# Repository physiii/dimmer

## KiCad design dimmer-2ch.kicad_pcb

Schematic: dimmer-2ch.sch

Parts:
J1: Conn_01x07; PinHeader_1x07_P2.54mm_Vertical
J2: Conn_01x03; SolderWirePad_1x03_P7.62mm_Drill2.5mm
J3: Conn_01x03; PinHeader_1x03_P2.54mm_Vertical

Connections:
/5V: J1.3, J1.4; also elsewhere on the board
/LINE_IN: J2.2, J3.3; also elsewhere on the board
/LINE_OUT_1: J2.3; also elsewhere on the board
/LINE_OUT_2: J2.1; also elsewhere on the board
/NEUTRAL: J3.1, J3.2; also elsewhere on the board
GND: J1.1, J1.2; also elsewhere on the board

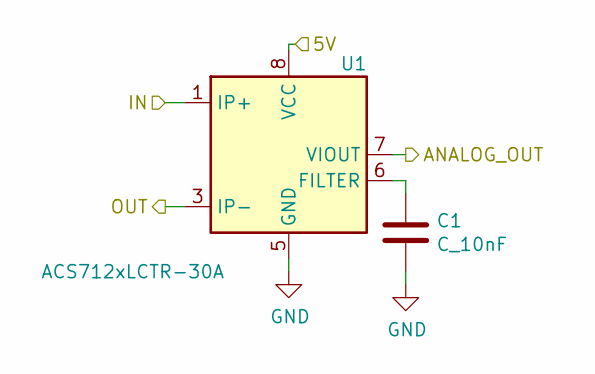
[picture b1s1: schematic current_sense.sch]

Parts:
C1: C_10nF; C_0603_1608Metric_Pad1.05x0.95mm_HandSolder; Part Number CL10B105KP8NNNC
U1: ACS712xLCTR-30A; SOIC-8_3.9x4.9mm_P1.27mm

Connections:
/5V: U1.8 (VCC); also elsewhere on the board
/CURRENT_SENSE_1: U1.7 (VIOUT); also elsewhere on the board
/LINE_OUT_1: U1.3 (IP-), U1.4 (IP-); also elsewhere on the board
/current sense 1/IN: U1.1 (IP+), U1.2 (IP+); also elsewhere on the board
GND: C1.2, U1.5 (GND); also elsewhere on the board
unnamed: C1.1, U1.6 (FILTER)

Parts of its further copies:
C3: C_10nF; C_0603_1608Metric_Pad1.05x0.95mm_HandSolder; Part Number CL10B105KP8NNNC
U4: ACS712xLCTR-30A; SOIC-8_3.9x4.9mm_P1.27mm

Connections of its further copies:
/5V: U4.8 (VCC); also elsewhere on the board
/CURRENT_SENSE_2: U4.7 (VIOUT); also elsewhere on the board
/LINE_OUT_2: U4.3 (IP-), U4.4 (IP-); also elsewhere on the board
/current sense 2/IN: U4.1 (IP+), U4.2 (IP+); also elsewhere on the board
GND: C3.2, U4.5 (GND); also elsewhere on the board
unnamed: C3.1, U4.6 (FILTER)

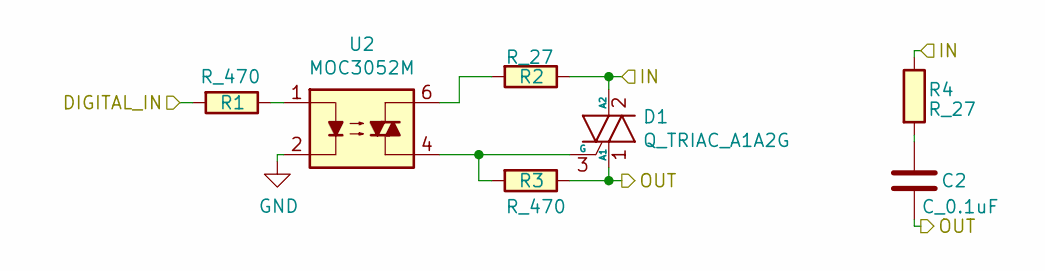
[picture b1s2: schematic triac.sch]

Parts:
C2: C_0.1uF; C_0603_1608Metric_Pad1.05x0.95mm_HandSolder; Part Number CL10F104ZO8NNNC
D1: Q_TRIAC_A1A2G; TO-263-2; Part Number BTA225B-600B,118
R1, R3: R_470; R_0603_1608Metric_Pad1.05x0.95mm_HandSolder; Part Number RC0603FR-07470RL
R2, R4: R_27; R_0603_1608Metric_Pad1.05x0.95mm_HandSolder; Part Number ERJ-3GEYJ270V
U2: MOC3052M; SMDIP-6_W9.53mm_Clearance8mm; Part Number MOC3052SM

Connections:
/LINE_IN: D1.2 (A2), R2.1, R4.1; also elsewhere on the board
/TRIAC_1: R1.2; also elsewhere on the board
/current sense 1/IN: C2.2, D1.1 (A1), R3.1; also elsewhere on the board
GND: U2.2; also elsewhere on the board
unnamed: C2.1, R4.2
unnamed: D1.3 (G), R3.2, U2.4
unnamed: R1.1, U2.1
unnamed: R2.2, U2.6

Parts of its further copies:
C4: C_0.1uF; C_0603_1608Metric_Pad1.05x0.95mm_HandSolder; Part Number CL10F104ZO8NNNC
D2: Q_TRIAC_A1A2G; TO-263-2; Part Number BTA225B-600B,118
R10, R12: R_470; R_0603_1608Metric_Pad1.05x0.95mm_HandSolder; Part Number RC0603FR-07470RL
R11, R13: R_27; R_0603_1608Metric_Pad1.05x0.95mm_HandSolder; Part Number ERJ-3GEYJ270V
U5: MOC3052M; SMDIP-6_W9.53mm_Clearance8mm; Part Number MOC3052SM

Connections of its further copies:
/LINE_IN: D2.2 (A2), R11.1, R13.1; also elsewhere on the board
/TRIAC_2: R10.2; also elsewhere on the board
/current sense 2/IN: C4.2, D2.1 (A1), R12.1; also elsewhere on the board
GND: U5.2; also elsewhere on the board
unnamed: C4.1, R13.2
unnamed: D2.3 (G), R12.2, U5.4
unnamed: R10.1, U5.1
unnamed: R11.2, U5.6

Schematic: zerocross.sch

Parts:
R5, R6, R7, R8, R9: R_10k; R_0603_1608Metric_Pad1.05x0.95mm_HandSolder; Part Number MCT06030C1002FP500
U3: H11AA1; DIP-6_W8.89mm_SMDSocket_LongPads; Part Number H11AA1SM

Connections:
/5V: R8.1; also elsewhere on the board
/LINE_IN: R5.2; also elsewhere on the board
/NEUTRAL: R6.2; also elsewhere on the board
/ZEROCROSS: R7.1, U3.5; also elsewhere on the board
GND: R9.2, U3.4; also elsewhere on the board
unnamed: R5.1, U3.1
unnamed: R6.1, U3.2
unnamed: R7.2, R8.2, R9.1

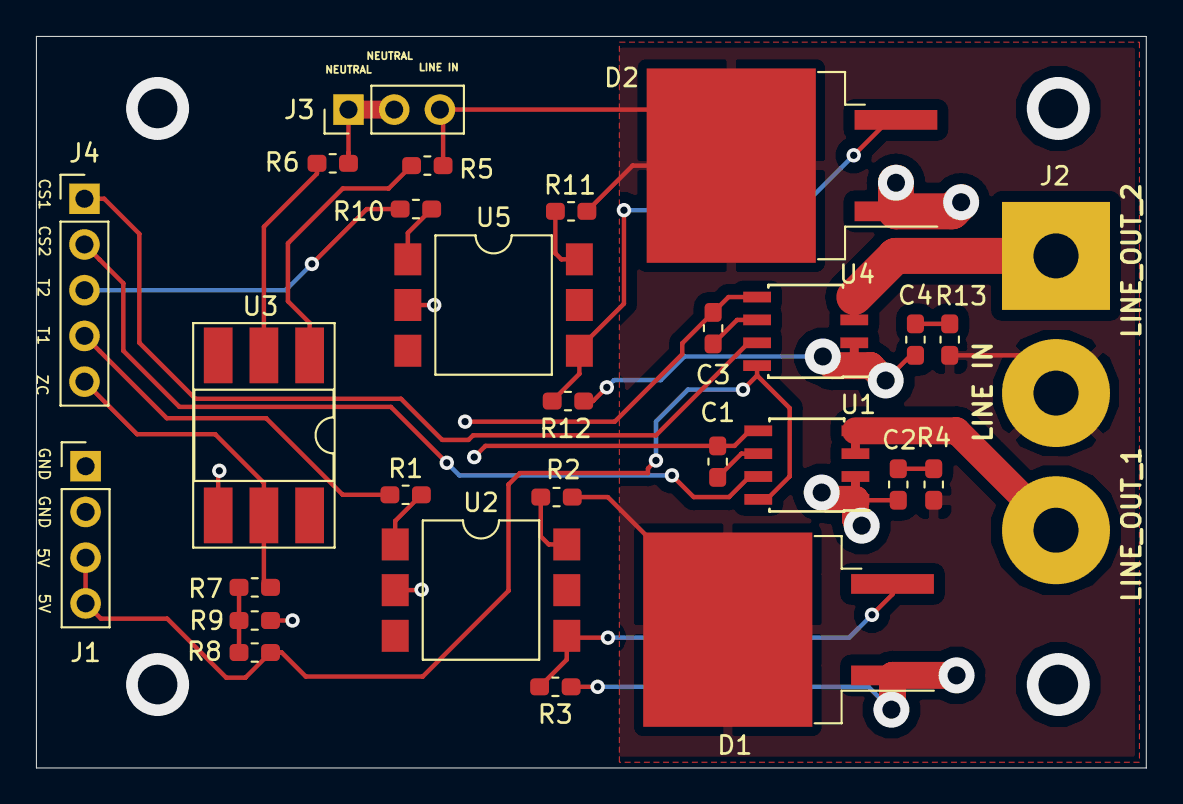
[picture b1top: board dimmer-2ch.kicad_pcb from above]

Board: 2 copper layers, 61.7 x 40.6 mm, 29 parts (1 on the bottom side), 26 nets.

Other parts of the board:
J4: Conn_01x05; PinHeader_1x05_P2.54mm_Vertical
LOGO: LOGO

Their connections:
/CURRENT_SENSE_1: J4.2; also elsewhere on the board
/CURRENT_SENSE_2: J4.1; also elsewhere on the board
/TRIAC_1: J4.4; also elsewhere on the board
/TRIAC_2: J4.3; also elsewhere on the board
/ZEROCROSS: J4.5; also elsewhere on the board

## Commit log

2018-11-18 first
2018-11-18 started layout
2018-11-19 finished layout, final check
2018-11-19 increased clearences
2018-11-19 ready for board house
